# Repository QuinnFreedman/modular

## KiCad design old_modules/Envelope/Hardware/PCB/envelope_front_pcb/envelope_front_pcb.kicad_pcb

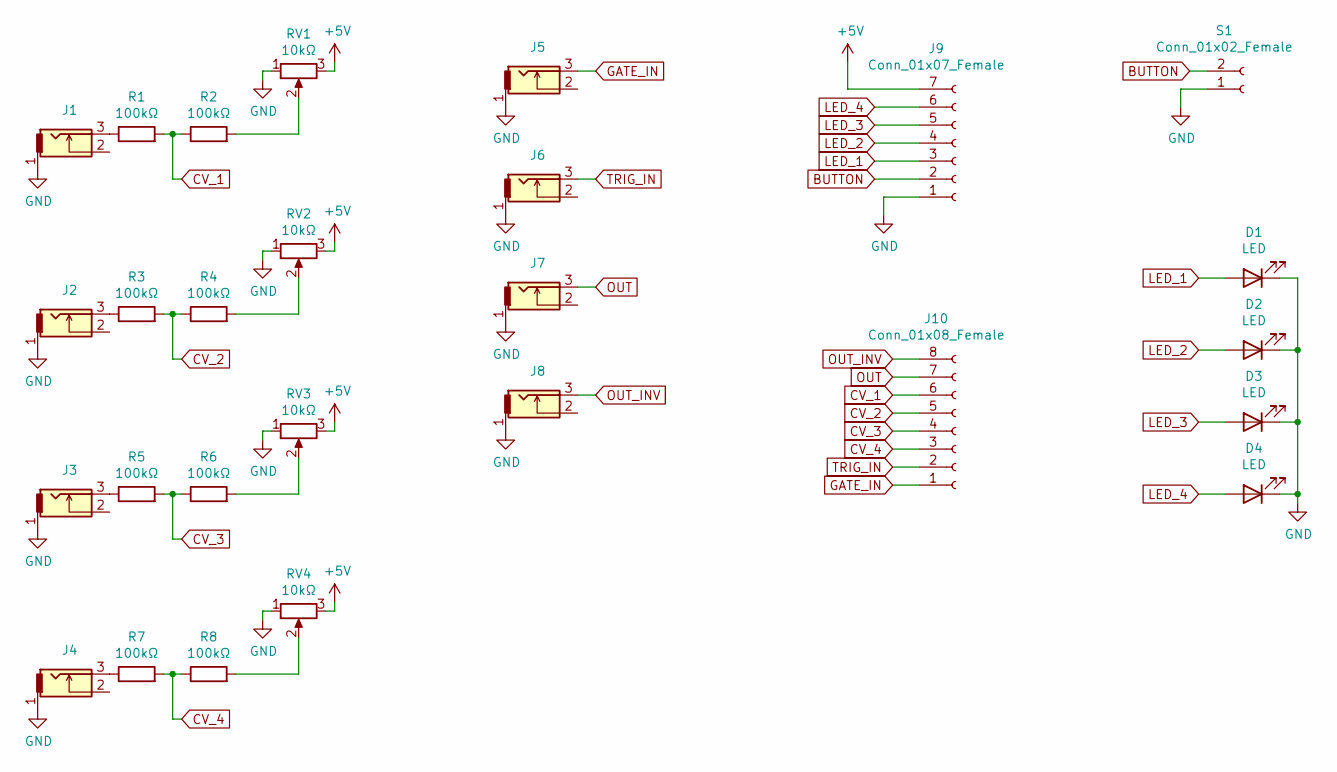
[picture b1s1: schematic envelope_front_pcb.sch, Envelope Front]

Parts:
D1, D2, D3, D4: LED; LED_D3.0mm_Clear
J1, J2, J3, J4, J5, J6, J7, J8: THONKICONN
J9: Conn_01x07_Female; PinSocket_1x07_P2.54mm_Vertical
J10: Conn_01x08_Female; PinSocket_1x08_P2.54mm_Vertical
R1, R2, R3, R4, R5, R6, R7, R8: 100kΩ; R_Axial_DIN0207_L6.3mm_D2.5mm_P10.16mm_Horizontal
RV1, RV2, RV3, RV4: 10kΩ; Potentiometer_Alpha_RD901F-40-00D_Single_Vertical
S1: Conn_01x02_Female; SolderWire-0.5sqmm_1x02_P4.8mm_D0.9mm_OD2.3mm

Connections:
+5V: J9.7, RV1.3, RV2.3, RV3.3, RV4.3
BUTTON: J9.2, S1.2
CV_1: J10.6, R1.2, R2.1
CV_2: J10.5, R3.2, R4.1
CV_3: J10.4, R5.2, R6.1
CV_4: J10.3, R7.2, R8.1
GATE_IN: J5.3, J10.1
GND: D1.1 (K), D2.1 (K), D3.1 (K), D4.1 (K), J1.1, J2.1, J3.1, J4.1, J5.1, J6.1, J7.1, J8.1, J9.1, RV1.1, RV2.1, RV3.1, RV4.1, S1.1
LED_1: D1.2 (A), J9.3
LED_2: D2.2 (A), J9.4
LED_3: D3.2 (A), J9.5
LED_4: D4.2 (A), J9.6
unnamed: J1.3, R1.1
unnamed: J2.3, R3.1
unnamed: J3.3, R5.1
unnamed: J4.3, R7.1
unnamed: R2.2, RV1.2
unnamed: R4.2, RV2.2
unnamed: R6.2, RV3.2
unnamed: R8.2, RV4.2
OUT: J7.3, J10.7
OUT_INV: J8.3, J10.8
TRIG_IN: J6.3, J10.2

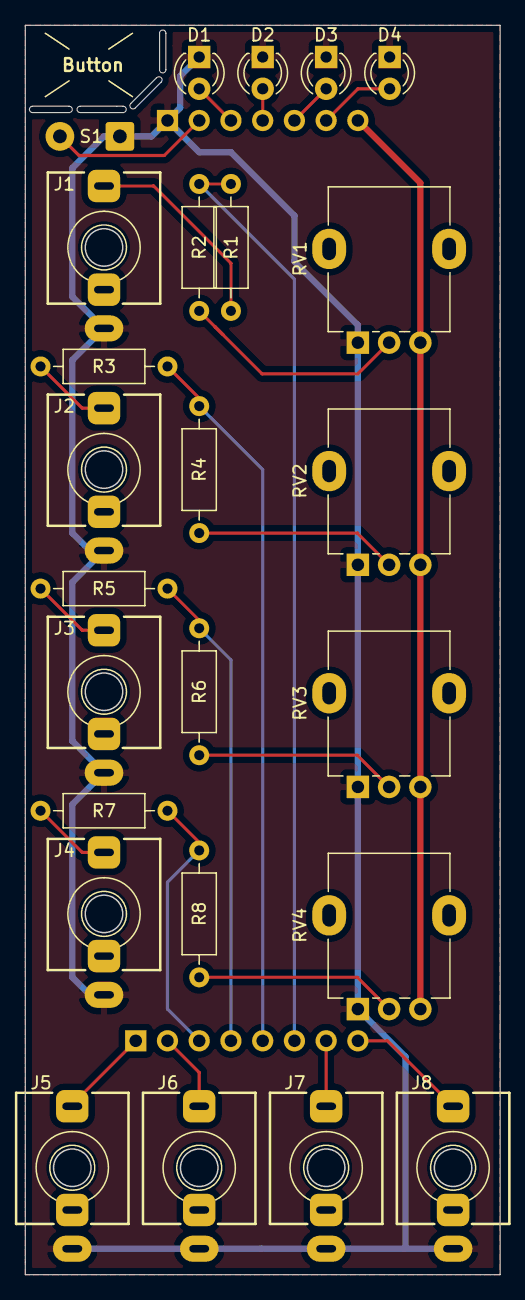
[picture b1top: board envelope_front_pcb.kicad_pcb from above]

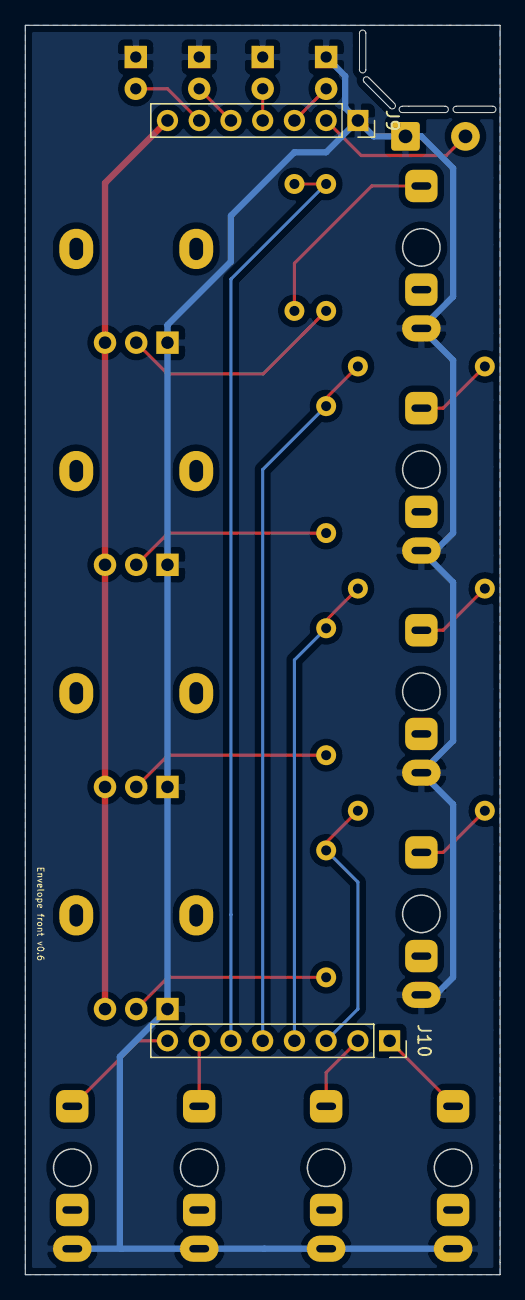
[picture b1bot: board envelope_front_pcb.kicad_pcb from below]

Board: 2 copper layers, 38.0 x 100.0 mm, 27 parts (2 on the bottom side), 23 nets.

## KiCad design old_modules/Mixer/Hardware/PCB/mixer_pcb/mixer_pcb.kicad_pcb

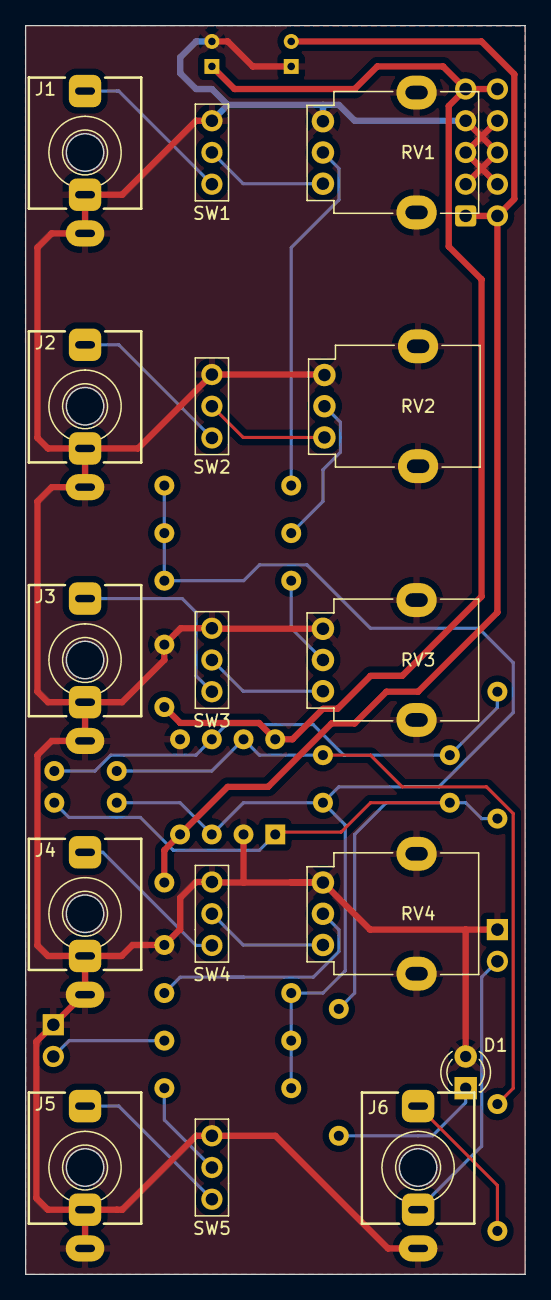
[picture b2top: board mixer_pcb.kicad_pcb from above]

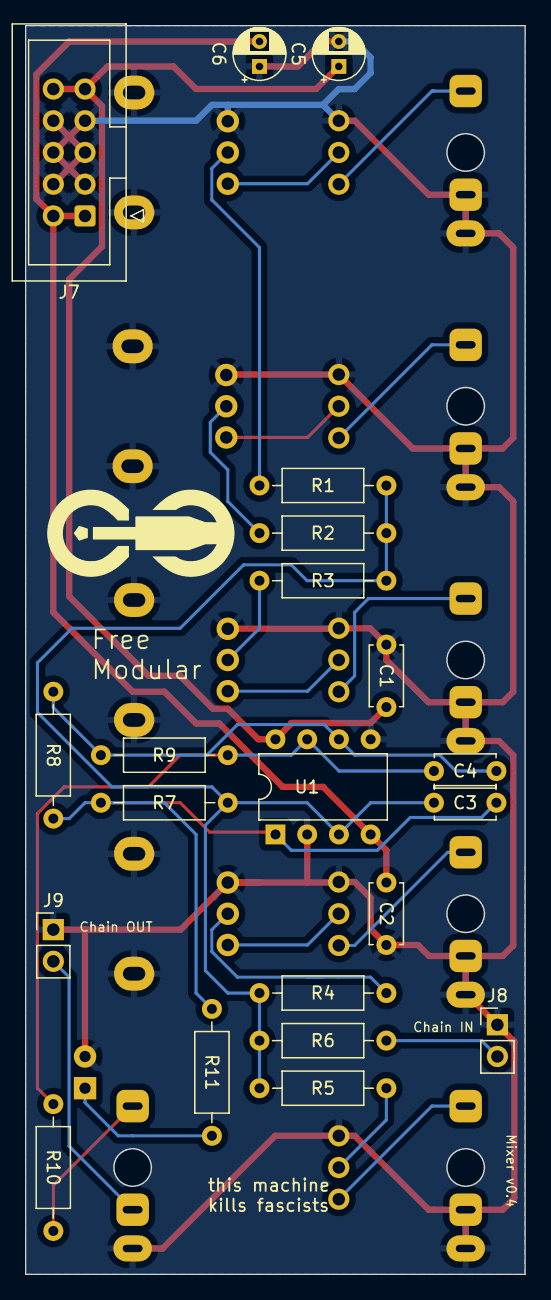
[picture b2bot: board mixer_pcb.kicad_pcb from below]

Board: 2 copper layers, 40.0 x 100.0 mm, 37 parts (21 on the bottom side), 25 nets.

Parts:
C1, C2: 100nF; C_Disc_D4.7mm_W2.5mm_P5.00mm
C3, C4: 100pF; C_Disc_D4.7mm_W2.5mm_P5.00mm
C5, C6: 10uF; CP_Radial_D4.0mm_P2.00mm
D1: LED; LED_D3.0mm
J1, J2, J3, J4, J5, J6: THONKICONN
J7: Eurorack_2x5_Power; IDC-Header_2x05_P2.54mm_Vertical
J8, J9: Conn_01x02_Socket; PinHeader_1x02_P2.54mm_Vertical
R1, R2, R3, R4, R5, R6, R7, R8, R9: 100kΩ; R_Axial_DIN0207_L6.3mm_D2.5mm_P10.16mm_Horizontal
R10: 1kΩ; R_Axial_DIN0207_L6.3mm_D2.5mm_P10.16mm_Horizontal
R11: 470Ω; R_Axial_DIN0207_L6.3mm_D2.5mm_P10.16mm_Horizontal
RV1, RV2, RV3, RV4: R_Potentiometer; Alpha_Potentiometer_Grounded
SW1, SW2, SW3, SW4, SW5: TAIWAY 200CWMSP1T3B4M2
U1: Opamp_Dual; DIP-8_W7.62mm

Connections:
+12V: C1.1, C5.1, J7.9 (+12v), J7.10 (+12v), U1.8 (V+)
-12V: C2.1, C6.2, J7.1 (-12v), J7.2 (-12v), U1.4 (V-)
GND: C1.2, C2.2, C5.2, C6.1, D1.2 (A), J1.1, J1.2, J2.1, J2.2, J3.1, J3.2, J4.1, J4.2, J5.1, J5.2, J6.1, J7.3 (GND), J7.4 (GND), J7.5 (GND), J7.6 (GND), J7.7 (GND), J7.8 (GND), J8.1, J9.1, RV1.1, RV1.MP, RV2.1, RV2.MP, RV3.1, RV3.MP, RV4.1, RV4.MP, SW1.3 (C), SW2.3 (C), SW3.3 (C), SW4.3 (C), SW5.3 (C), U1.2 (-), U1.5 (+)
unnamed: C3.2, R7.2, R8.1, R11.2, U1.1
unnamed: C4.2, R9.2, R10.1, U1.7
unnamed: D1.1 (K), R11.1
unnamed: J6.3, R10.2
unnamed: J8.2, R6.1
unnamed: J6.2, J9.2
unnamed: R1.1, RV1.2
unnamed: R2.1, RV2.2
unnamed: R3.1, RV3.2
unnamed: R4.1, RV4.2
unnamed: J1.3, SW1.1 (A)
unnamed: RV1.3, SW1.2 (B)
unnamed: J2.3, SW2.1 (A)
unnamed: RV2.3, SW2.2 (B)
unnamed: J3.3, SW3.1 (A)
unnamed: RV3.3, SW3.2 (B)
unnamed: J4.3, SW4.1 (A)
unnamed: RV4.3, SW4.2 (B)
unnamed: J5.3, SW5.1 (A)
unnamed: R5.1, SW5.2 (B)
unnamed: C3.1, R1.2, R2.2, R3.2, R4.2, R5.2, R6.2, R7.1, U1.3 (+)
unnamed: C4.1, R8.2, R9.1, U1.6 (-)

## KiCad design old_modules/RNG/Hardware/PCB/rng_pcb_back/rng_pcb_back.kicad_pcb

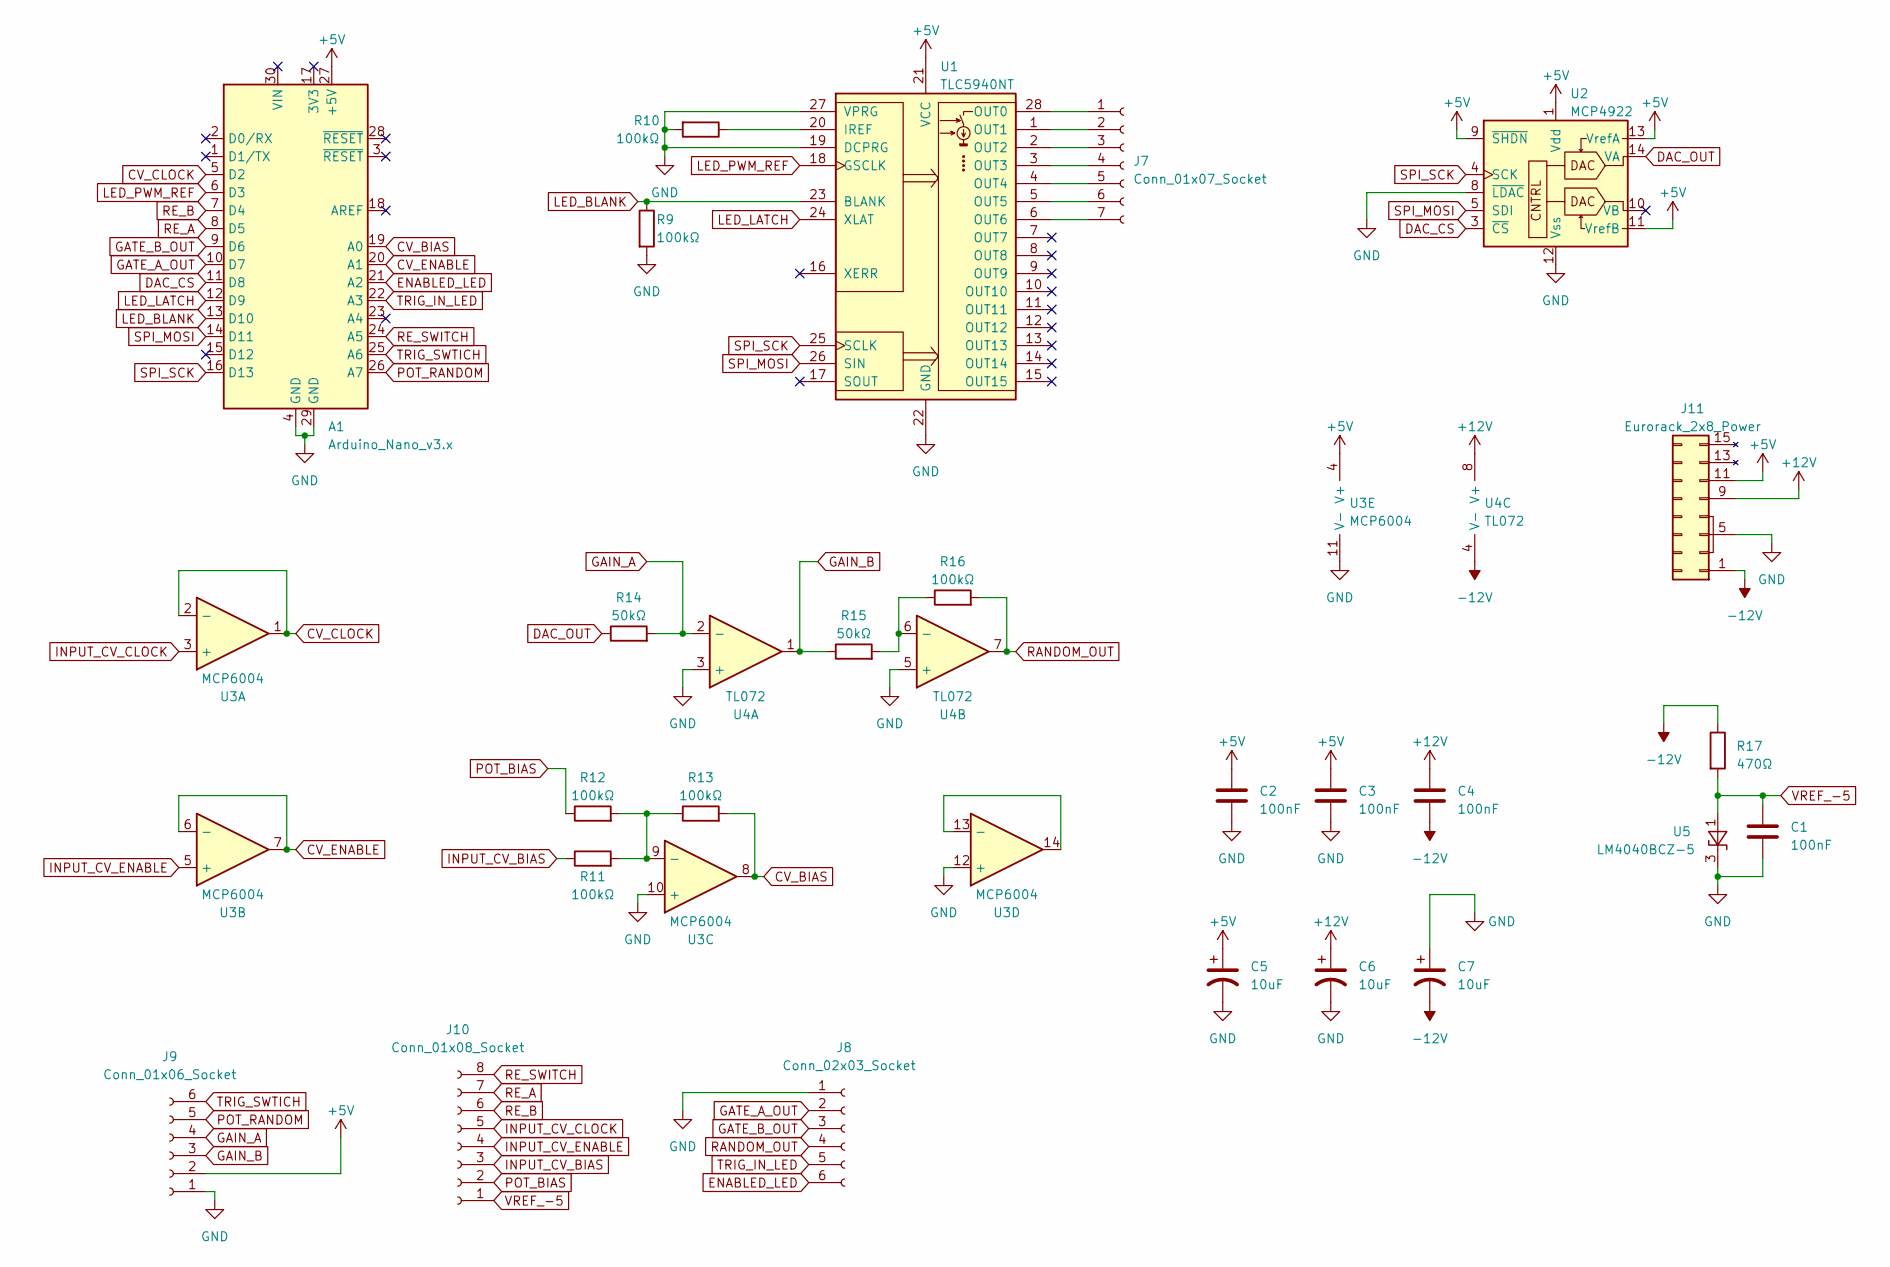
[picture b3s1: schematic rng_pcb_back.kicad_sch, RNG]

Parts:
A1: Arduino_Nano_v3.x; Arduino_Nano
C1, C2, C3, C4: 100nF; C_Disc_D5.0mm_W2.5mm_P5.00mm
C5, C6, C7: 10uF; CP_Radial_D4.0mm_P1.50mm
J7: Conn_01x07_Socket; PinHeader_1x07_P2.54mm_Vertical
J8: Conn_02x03_Socket; PinHeader_2x03_P2.54mm_Vertical
J9: Conn_01x06_Socket; PinHeader_1x06_P2.54mm_Vertical
J10: Conn_01x08_Socket; PinHeader_1x08_P2.54mm_Vertical
J11: Eurorack_2x8_Power; IDC-Header_2x08_P2.54mm_Vertical
R9, R10, R11, R12, R13, R16: 100kΩ; R_Axial_DIN0207_L6.3mm_D2.5mm_P7.62mm_Horizontal
R14, R15: 50kΩ; R_Axial_DIN0207_L6.3mm_D2.5mm_P7.62mm_Horizontal
R17: 470Ω; R_Axial_DIN0207_L6.3mm_D2.5mm_P7.62mm_Horizontal
U1: TLC5940NT; DIP-28_W7.62mm
U2: MCP4922; DIP-14_W7.62mm
U3: MCP6004; DIP-14_W7.62mm
U4: TL072; DIP-8_W7.62mm
U5: LM4040BCZ-5; TO-92L_Inline_Wide

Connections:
+5V: A1.27 (+5V), C2.1, C3.1, C5.1, J9.2, J11.11 (+5v), J11.12 (+5v), U1.21 (VCC), U2.1 (Vdd), U2.9 (~SHDN), U2.11 (VrefB), U2.13 (VrefA), U3.4 (V+)
+12V: C4.1, C6.1, J11.9 (+12v), J11.10 (+12v), U4.8 (V+)
-12V: C4.2, C7.2, J11.1 (-12v), J11.2 (-12v), R17.1, U4.4 (V-)
CV_BIAS: A1.19 (A0), R13.2, U3.8
CV_CLOCK: A1.5 (D2), U3.1, U3.2 (-)
CV_ENABLE: A1.20 (A1), U3.6 (-), U3.7
DAC_CS: A1.11 (D8), U2.3 (~CS)
DAC_OUT: R14.1, U2.14 (VA)
ENABLED_LED: A1.21 (A2), J8.6
GAIN_A: J9.4, R14.2, U4.2 (-)
GAIN_B: J9.3, R15.1, U4.1
GATE_A_OUT: A1.10 (D7), J8.2
GATE_B_OUT: A1.9 (D6), J8.3
GND: A1.4 (GND), A1.29 (GND), C1.2, C2.2, C3.2, C5.2, C6.2, C7.1, J8.1, J9.1, J11.3 (GND), J11.4 (GND), J11.5 (GND), J11.6 (GND), J11.7 (GND), J11.8 (GND), R9.2, R10.2, U1.19 (DCPRG), U1.22 (GND), U1.27 (VPRG), U2.8 (~LDAC), U2.12 (Vss), U3.10 (+), U3.11 (V-), U3.12 (+), U4.3 (+), U4.5 (+), U5.3 (K)
INPUT_CV_BIAS: J10.3, R11.1
INPUT_CV_CLOCK: J10.5, U3.3 (+)
INPUT_CV_ENABLE: J10.4, U3.5 (+)
LED_BLANK: A1.13 (D10), R9.1, U1.23 (BLANK)
LED_LATCH: A1.12 (D9), U1.24 (XLAT)
LED_PWM_REF: A1.6 (D3), U1.18 (GSCLK)
unnamed: J7.1, U1.28 (OUT0)
unnamed: J7.2, U1.1 (OUT1)
unnamed: J7.3, U1.2 (OUT2)
unnamed: J7.4, U1.3 (OUT3)
unnamed: J7.5, U1.4 (OUT4)
unnamed: J7.6, U1.5 (OUT5)
unnamed: J7.7, U1.6 (OUT6)
unnamed: R10.1, U1.20 (IREF)
unnamed: R11.2, R12.2, R13.1, U3.9 (-)
unnamed: U3.13 (-), U3.14
unnamed: R15.2, R16.1, U4.6 (-)
POT_BIAS: J10.2, R12.1
POT_RANDOM: A1.26 (A7), J9.5
RANDOM_OUT: J8.4, R16.2, U4.7
RE_A: A1.8 (D5), J10.7
RE_B: A1.7 (D4), J10.6
RE_SWITCH: A1.24 (A5), J10.8
SPI_MOSI: A1.14 (D11), U1.26 (SIN), U2.5 (SDI)
SPI_SCK: A1.16 (D13), U1.25 (SCLK), U2.4 (SCK)
TRIG_IN_LED: A1.22 (A3), J8.5
TRIG_SWTICH: A1.25 (A6), J9.6
VREF_-5: C1.1, J10.1, R17.2, U5.1 (A)

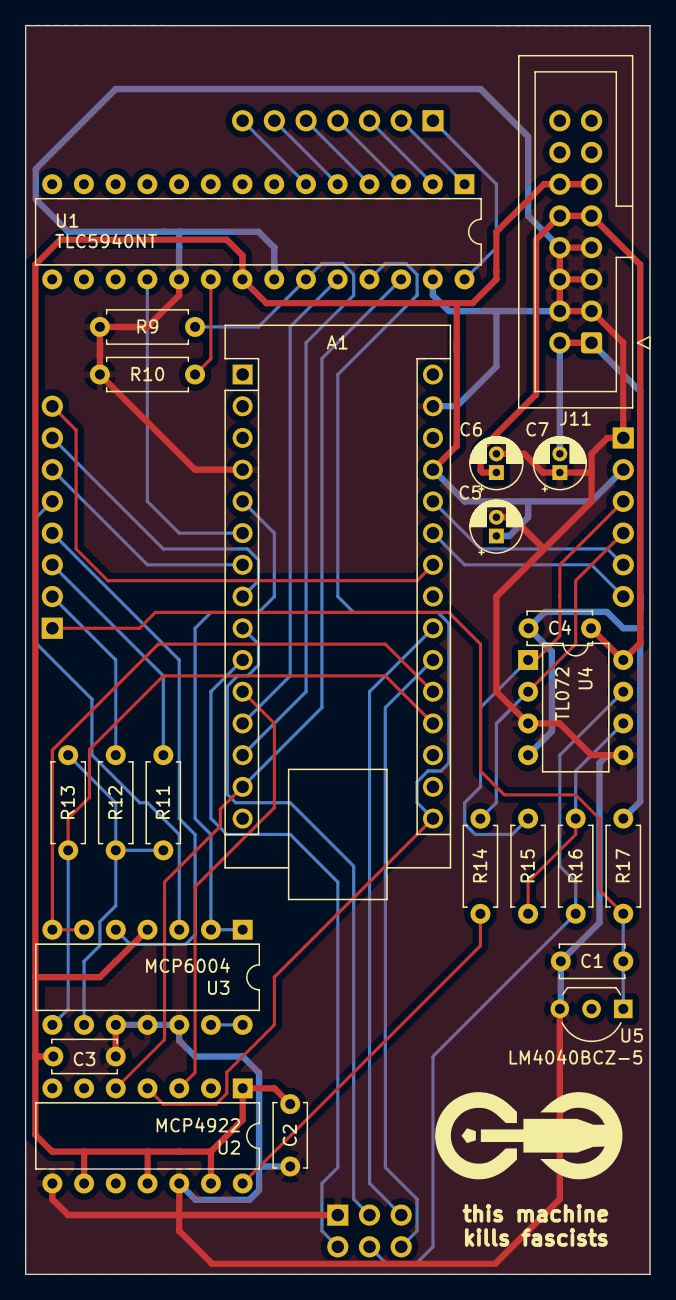
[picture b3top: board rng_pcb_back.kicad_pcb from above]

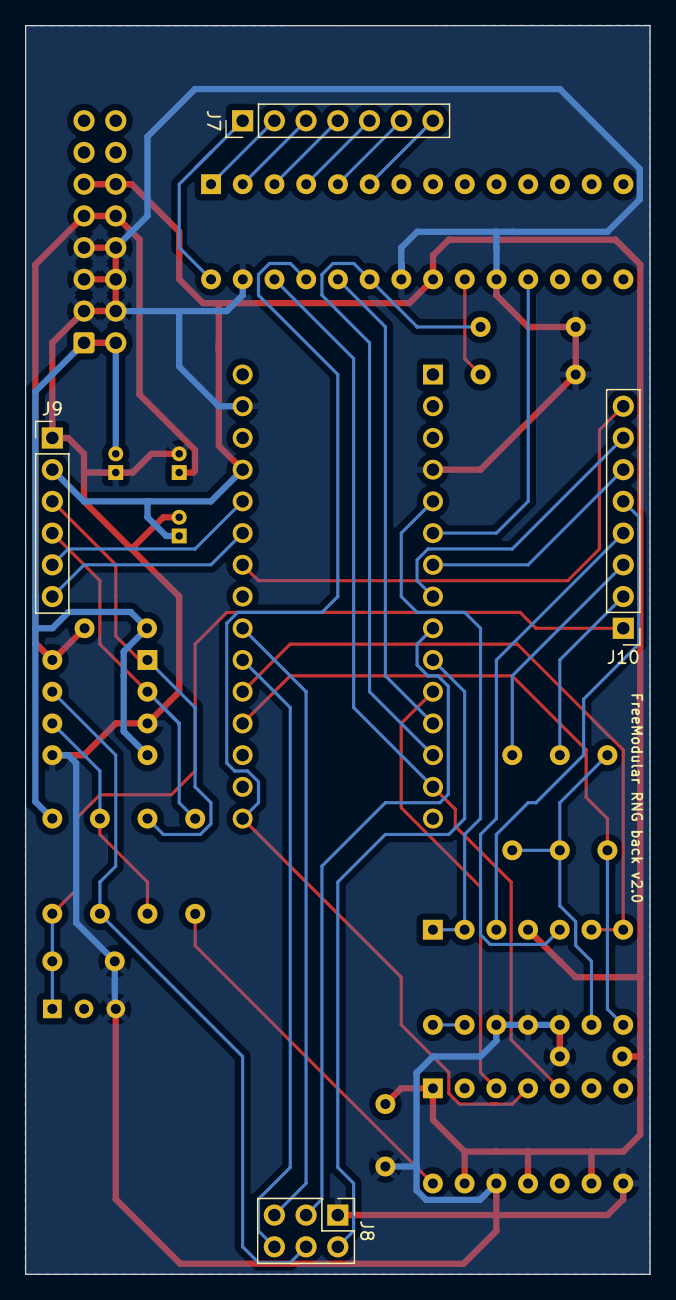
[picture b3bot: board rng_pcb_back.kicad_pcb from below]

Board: 2 copper layers, 50.0 x 100.0 mm, 27 parts (4 on the bottom side), 42 nets.

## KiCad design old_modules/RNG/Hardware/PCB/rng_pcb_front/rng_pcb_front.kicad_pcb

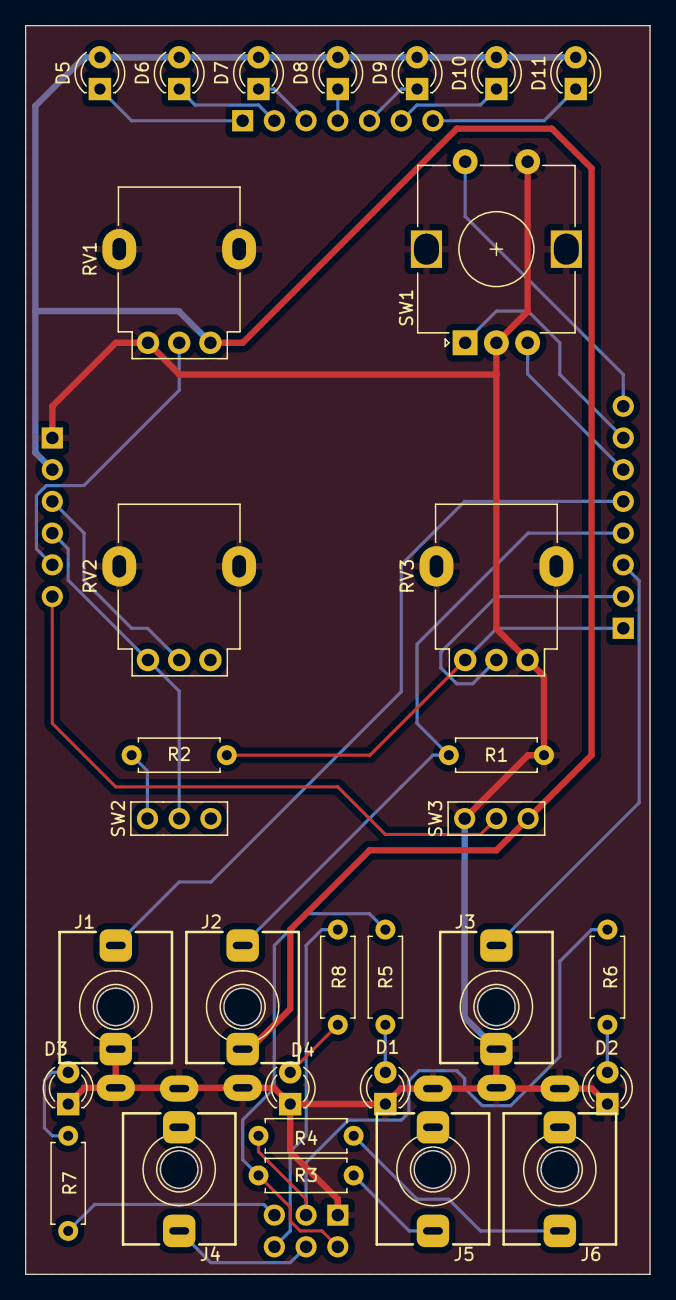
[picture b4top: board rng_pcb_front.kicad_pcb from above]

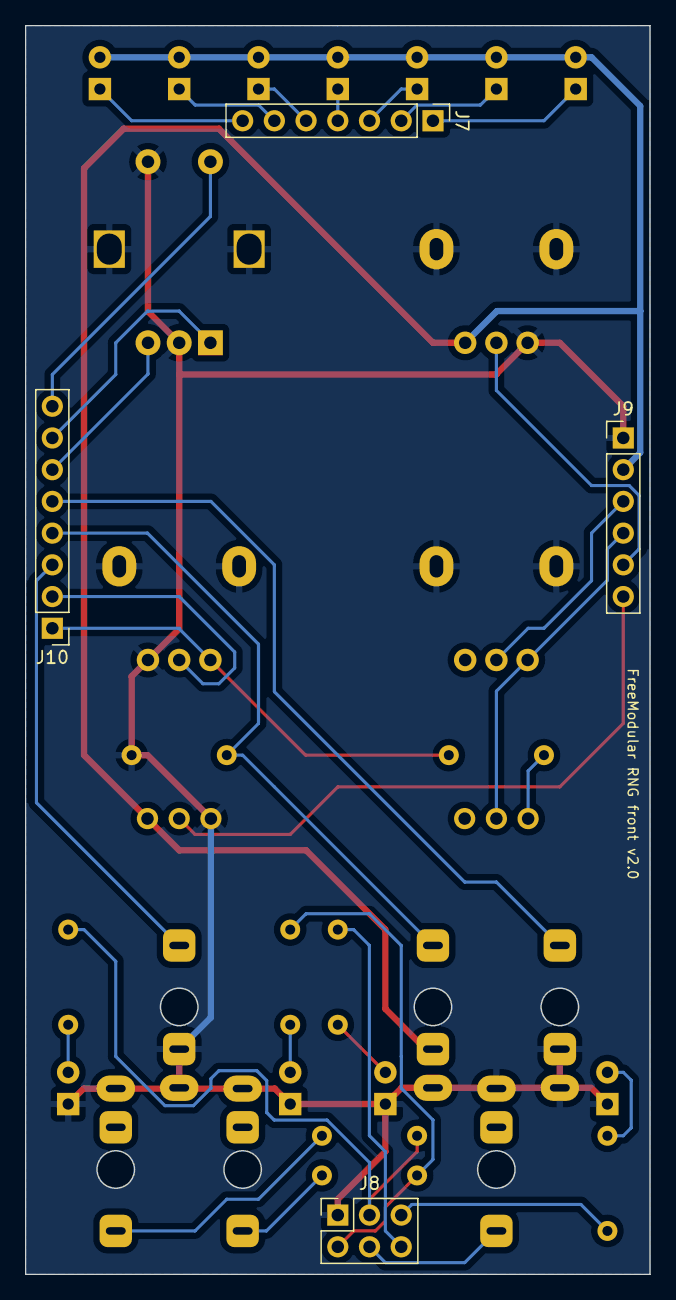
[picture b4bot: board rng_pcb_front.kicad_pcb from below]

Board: 2 copper layers, 50.0 x 100.0 mm, 35 parts (4 on the bottom side), 33 nets.

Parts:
D1, D2, D3, D4, D5, D6, D7, D8, D9, D10, D11: LED; LED_D3.0mm
J1, J2, J3, J4, J5, J6: THONKICONN
J7: Conn_01x07_Pin; PinHeader_1x07_P2.54mm_Vertical
J8: Conn_02x03_Pin; PinHeader_2x03_P2.54mm_Vertical
J9: Conn_01x06_Pin; PinHeader_1x06_P2.54mm_Vertical
J10: Conn_01x08_Pin; PinHeader_1x08_P2.54mm_Vertical
R1, R2: 100k; R_Axial_DIN0207_L6.3mm_D2.5mm_P7.62mm_Horizontal
R3, R4, R5, R6, R7, R8: 1k; R_Axial_DIN0207_L6.3mm_D2.5mm_P7.62mm_Horizontal
RV1, RV2, RV3: Linear 50k; Alpha_Potentiometer_Grounded
SW1: RotaryEncoder_Switch; RotaryEncoder_Alps_EC12E-Switch_Vertical_H20mm
SW2, SW3: TAIWAY 200CWMSP1T3B4M2

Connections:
+5V: D5.2 (A), D6.2 (A), D7.2 (A), D8.2 (A), D9.2 (A), D10.2 (A), D11.2 (A), J2.2, J9.2, RV1.3, SW3.3 (C)
ENABLED_LED: J8.6, R8.1
GAIN_A: J9.4, RV2.1, SW2.2 (B)
GAIN_B: J9.3, RV2.2
GATE_A_OUT: J8.2, R3.1, R5.1
GATE_B_OUT: J8.3, R4.1, R6.1
GND: D1.1 (K), D2.1 (K), D3.1 (K), D4.1 (K), J1.1, J1.2, J2.1, J3.1, J3.2, J4.1, J5.1, J6.1, J8.1, J9.1, R1.2, RV1.1, RV1.MP, RV2.MP, RV3.3, RV3.MP, SW1.C, SW1.MP, SW1.S2, SW3.1 (A)
INPUT_CV_BIAS: J3.3, J10.3
INPUT_CV_CLOCK: J1.3, J10.5
INPUT_CV_ENABLE: J2.3, J10.4, R1.1
unnamed: D1.2 (A), R5.2
unnamed: D2.2 (A), R6.2
unnamed: D3.2 (A), R7.2
unnamed: D4.2 (A), R8.2
unnamed: D5.1 (K), J7.1
unnamed: D6.1 (K), J7.2
unnamed: D7.1 (K), J7.3
unnamed: D8.1 (K), J7.4
unnamed: D9.1 (K), J7.5
unnamed: D10.1 (K), J7.6
unnamed: D11.1 (K), J7.7
unnamed: J5.3, R3.2
unnamed: J6.3, R4.2
unnamed: R2.2, SW2.1 (A)
POT_BIAS: J10.2, RV3.2
POT_RANDOM: J9.5, RV1.2
RANDOM_OUT: J4.3, J8.4
RE_A: J10.7, SW1.A
RE_B: J10.6, SW1.B
RE_SWITCH: J10.8, SW1.S1
TRIG_IN_LED: J8.5, R7.1
TRIG_SWTICH: J9.6, SW3.2 (B)
VREF_-5: J10.1, R2.1, RV3.1

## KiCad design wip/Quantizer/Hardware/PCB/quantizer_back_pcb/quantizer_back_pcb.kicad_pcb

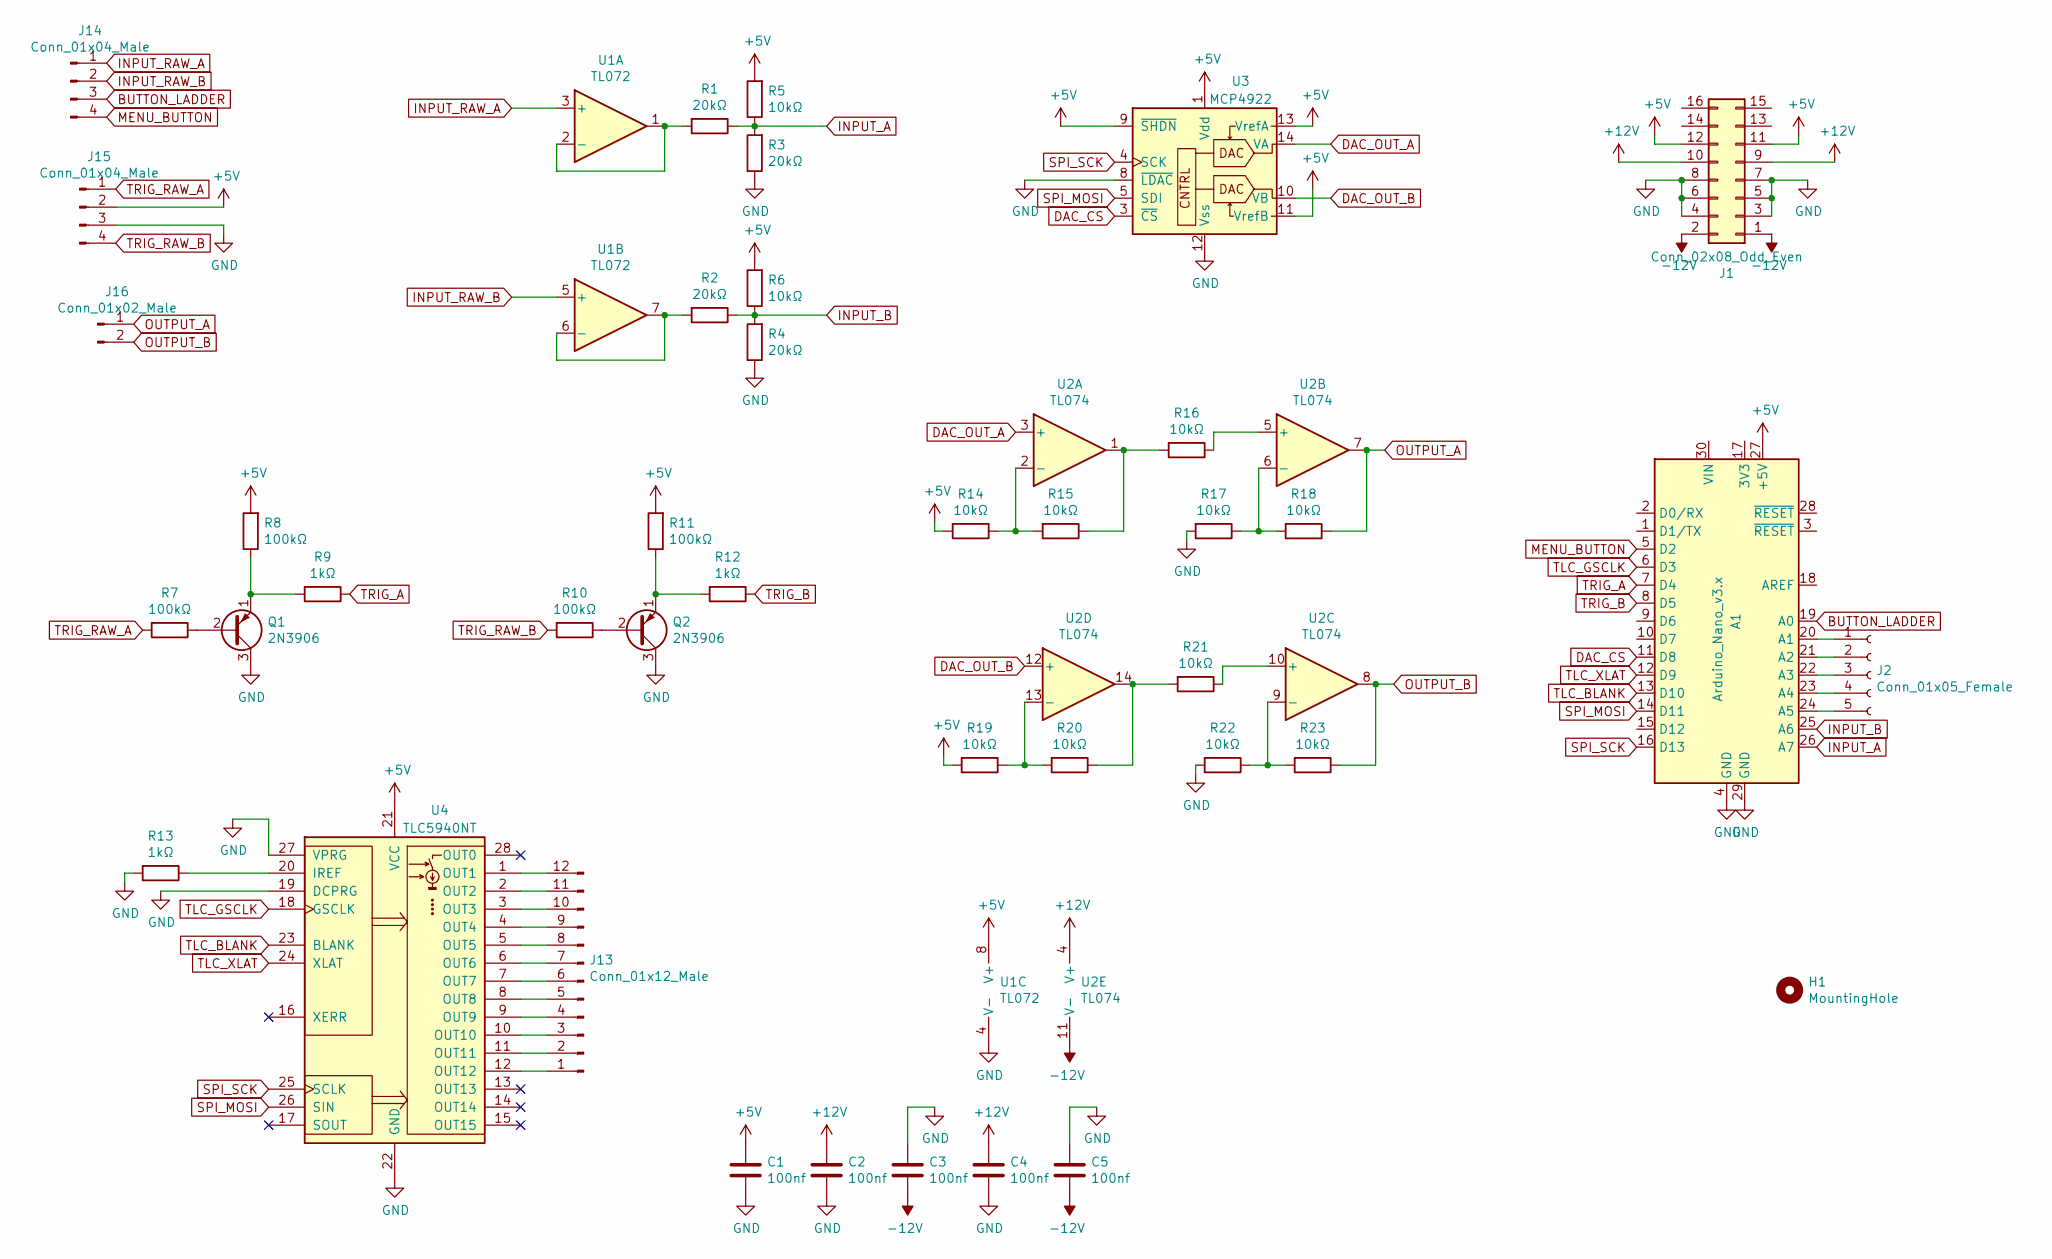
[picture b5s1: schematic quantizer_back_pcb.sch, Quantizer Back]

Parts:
A1: Arduino_Nano_v3.x; Arduino_Nano
C1, C2, C3, C4, C5: 100nf; C_Disc_D4.7mm_W2.5mm_P5.00mm
H1: MountingHole; MountingHole_2.7mm_M2.5
J1: Conn_02x08_Odd_Even; IDC-Header_2x08_P2.54mm_Vertical
J2: Conn_01x05_Female; PinHeader_1x05_P2.54mm_Vertical
J13: Conn_01x12_Male; PinHeader_1x12_P2.54mm_Vertical
J14, J15: Conn_01x04_Male; PinHeader_1x04_P2.54mm_Vertical
J16: Conn_01x02_Male; PinHeader_1x02_P2.54mm_Vertical
Q1, Q2: 2N3906; TO-92_Inline_Wide
R1, R2, R3, R4: 20kΩ; R_Axial_DIN0207_L6.3mm_D2.5mm_P10.16mm_Horizontal
R5, R6, R14, R15, R16, R17, R18, R19, R20, R21, R22, R23: 10kΩ; R_Axial_DIN0207_L6.3mm_D2.5mm_P10.16mm_Horizontal
R7, R8, R10, R11: 100kΩ; R_Axial_DIN0207_L6.3mm_D2.5mm_P10.16mm_Horizontal
R9, R12, R13: 1kΩ; R_Axial_DIN0207_L6.3mm_D2.5mm_P10.16mm_Horizontal
U1: TL072; DIP-8_W7.62mm
U2: TL074; DIP-14_W7.62mm
U3: MCP4922; DIP-14_W7.62mm
U4: TLC5940NT; DIP-28_W7.62mm

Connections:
BUTTON_LADDER: A1.19 (A0), J14.3
DAC_CS: A1.11 (D8), U3.3 (~CS)
DAC_OUT_A: U2.3 (+), U3.14 (VA)
DAC_OUT_B: U2.12 (+), U3.10 (VB)
INPUT_A: A1.26 (A7), R1.1, R3.2, R5.1
INPUT_B: A1.25 (A6), R2.1, R4.2, R6.1
INPUT_RAW_A: J14.1, U1.3 (+)
INPUT_RAW_B: J14.2, U1.5 (+)
MENU_BUTTON: A1.5 (D2), J14.4
unnamed: A1.20 (A1), J2.1
unnamed: A1.21 (A2), J2.2
unnamed: A1.22 (A3), J2.3
unnamed: A1.23 (A4), J2.4
unnamed: A1.24 (A5), J2.5
unnamed: J13.1, U4.12 (OUT12)
unnamed: J13.2, U4.11 (OUT11)
unnamed: J13.3, U4.10 (OUT10)
unnamed: J13.4, U4.9 (OUT9)
unnamed: J13.5, U4.8 (OUT8)
unnamed: J13.6, U4.7 (OUT7)
unnamed: J13.7, U4.6 (OUT6)
unnamed: J13.8, U4.5 (OUT5)
unnamed: J13.9, U4.4 (OUT4)
unnamed: J13.10, U4.3 (OUT3)
unnamed: J13.11, U4.2 (OUT2)
unnamed: J13.12, U4.1 (OUT1)
unnamed: Q1.1 (E), R8.1, R9.2
unnamed: Q1.2 (B), R7.1
unnamed: Q2.1 (E), R11.1, R12.2
unnamed: Q2.2 (B), R10.1
unnamed: R1.2, U1.1, U1.2 (-)
unnamed: R2.2, U1.6 (-), U1.7
unnamed: R13.1, U4.20 (IREF)
unnamed: R14.1, R15.2, U2.2 (-)
unnamed: R15.1, R16.2, U2.1
unnamed: R16.1, U2.5 (+)
unnamed: R17.1, R18.2, U2.6 (-)
unnamed: R19.1, R20.2, U2.13 (-)
unnamed: R20.1, R21.2, U2.14
unnamed: R21.1, U2.10 (+)
unnamed: R22.1, R23.2, U2.9 (-)
OUTPUT_A: J16.1, R18.1, U2.7
OUTPUT_B: J16.2, R23.1, U2.8
SPI_MOSI: A1.14 (D11), U3.5 (SDI), U4.26 (SIN)
SPI_SCK: A1.16 (D13), U3.4 (SCK), U4.25 (SCLK)
TLC_BLANK: A1.13 (D10), U4.23 (BLANK)
TLC_GSCLK: A1.6 (D3), U4.18 (GSCLK)
TLC_XLAT: A1.12 (D9), U4.24 (XLAT)
TRIG_A: A1.7 (D4), R9.1
TRIG_B: A1.8 (D5), R12.1
TRIG_RAW_A: J15.1, R7.2
TRIG_RAW_B: J15.4, R10.2

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
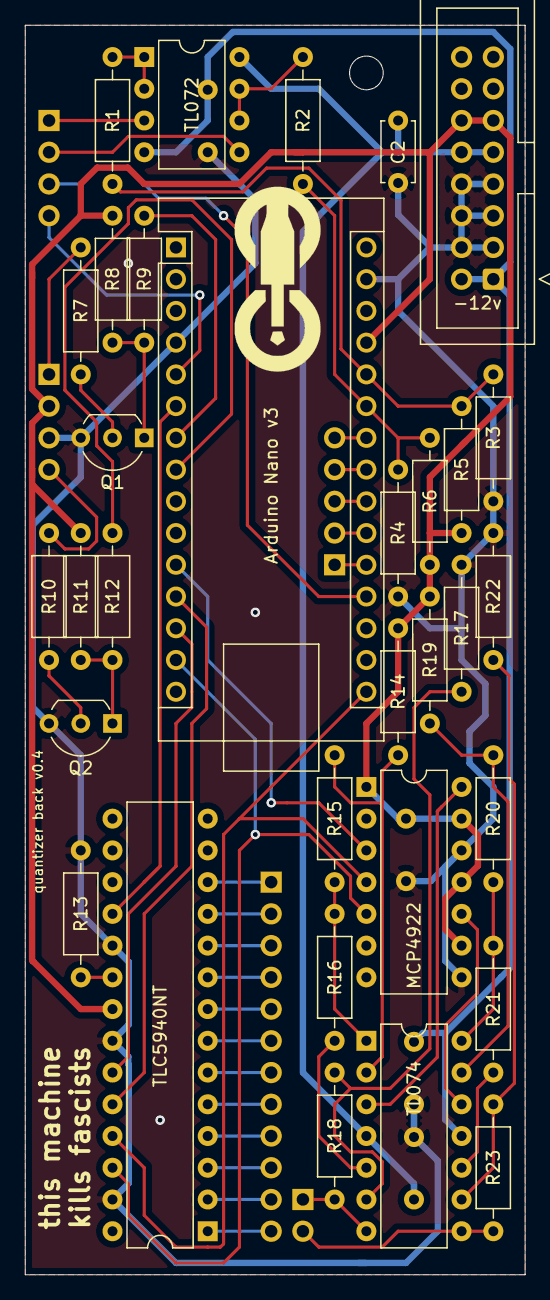
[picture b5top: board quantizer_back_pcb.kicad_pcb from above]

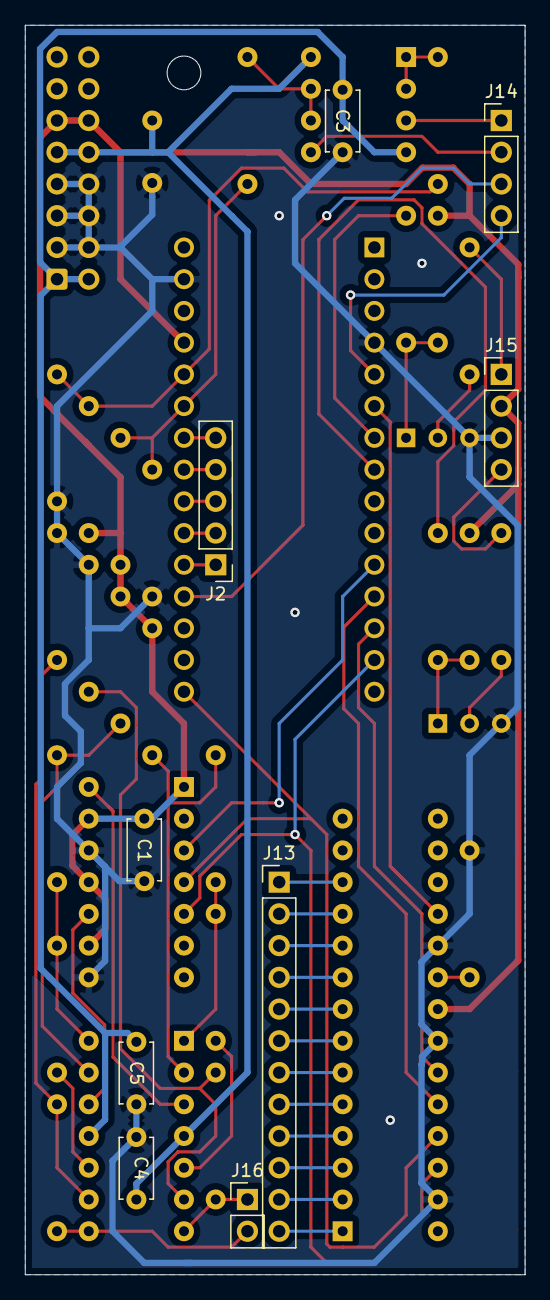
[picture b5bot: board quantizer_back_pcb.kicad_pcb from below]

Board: 2 copper layers, 40.0 x 100.0 mm, 42 parts (9 on the bottom side), 56 nets.
